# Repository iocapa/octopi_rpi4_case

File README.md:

Shield: [![CC BY-SA 4.0][cc-by-sa-shield]][cc-by-sa]

This work is licensed under a
[Creative Commons Attribution-ShareAlike 4.0 International License][cc-by-sa].

[![CC BY-SA 4.0][cc-by-sa-image]][cc-by-sa]

[cc-by-sa]: http://creativecommons.org/licenses/by-sa/4.0/
[cc-by-sa-image]: https://licensebuttons.net/l/by-sa/4.0/88x31.png
[cc-by-sa-shield]: https://img.shields.io/badge/License-CC%20BY--SA%204.0-lightgrey.svg

## Disclaimer ##
Working with mains voltage can be dangerous. Proceed at your own risk.

## Scope ##
* The scope of this project was to create a case for a raspberry pi4 that runs octopi and provides a way to turn off/on the printer (Prusa MK3S+) via the web interface. 
* The project was designed and built during a weekend, therefore it had to be built with parts/tools I had lying around, and it had to be pretty low effort.
* In retrospective, some design decisions were not the "best", but after running this for a week, I'm pretty satisfied with it :).

## Requirements ##
* Shall use a raspberry pi4.
* Shall be compact enough to fit the available space.
* Shall incorporate a relay controllable through the octoprint interface.
* Shall have a status LED.
* Shall have a safe shutdown / power-on button.
* Shall provide active cooling (fan).
* Shall be installable with minimal effort (no mods to the printer).

## Design (Day 1) ##
* ~~Design the [PCB](./pcb/octopi_rpi4_case.pro)~~.
* ~~Design the case [assembly](./assembly/assembly.pdf)~~.

## Build (Day 2) ##
* Print the [top](./pics/11-top.jpg) part of the case and install the brass inserts.
* Cut and [drill](./pics/1-drill.jpg) the blank PCB using the provided [stencil](./pcb/printable/hole_guide.stl).
* [Mask](./pics/2-mask.jpg) the PCB (with a quality permanent marker) using the [template](./pcb/octopi_rpi4_case_bot_mirrored.pdf).
* [Etch](./pics/3-etch.jpg) the PCB.
* [Tin](./pics/4-tin.jpg) the PCB.
* [Populate](./pics/5-assemble.jpg) the PCB using the [template](./pcb/octopi_rpi4_case_silk.pdf) and the [schematic](./pcb/octopi_rpi4_case.pdf).
* [Coat](./pics/6-coat.jpg) the PCB with a thick plastic layer using the provided [mask](./pcb/printable/coating_mask.stl). <span style="color:red">WARNING SKIP THIS AT YOUR OWN RISK</span>, [ECS Plastic 70](https://www.ecsag.com/product/plastic-2/?lang=en) spray works well.
* Print the [bottom](./pics/10-botom-cap.jpg) part of the case and install the brass inserts, print the switch cap.
* Add connectors to the fans and other cables (power and signal) using the [schematic](./pcb/octopi_rpi4_case.pdf) tables.
* [Prepare](./pics/7-parts.jpg) the parts.
* Assemble the [parts](./pics/8-pre.jpg).
* [Assemble](./pics/9-final.jpg) the case using the [video](./assembly/assembly.mp4) and the [instructions](./assembly/assembly.pdf).
* [Install](https://octoprint.org/download/) on your SD card.
* Copy [boot.txt](./software/boot.txt) and [config.txt](./software/config.txt) to the card. Install the card.
* Unplug the printer cord and connect it to the power input and connect the power output to the printer.
* Instal the [OctoRelay](https://plugins.octoprint.org/plugins/octorelay) plugin and configure the printer relay "GPIO Number" to 15.
* Have fun :)

## Special thanks to ##
* [Hasanain Shuja](https://grabcad.com/hasanain.shuja-1) for the RPi4 step model.
* [John Michael Loeffler](https://grabcad.com/john-772) for the Relay and JST connector step models.
* [KiCAD](https://www.kicad.org/), [Raspberry Pi Foundation](https://www.raspberrypi.org/) and [Fusion 360](https://www.autodesk.com/products/fusion-360/overview) for the awesome tools and resources.

## License ##
A [LICENSE](./LICENSE) file is provided with this repository.

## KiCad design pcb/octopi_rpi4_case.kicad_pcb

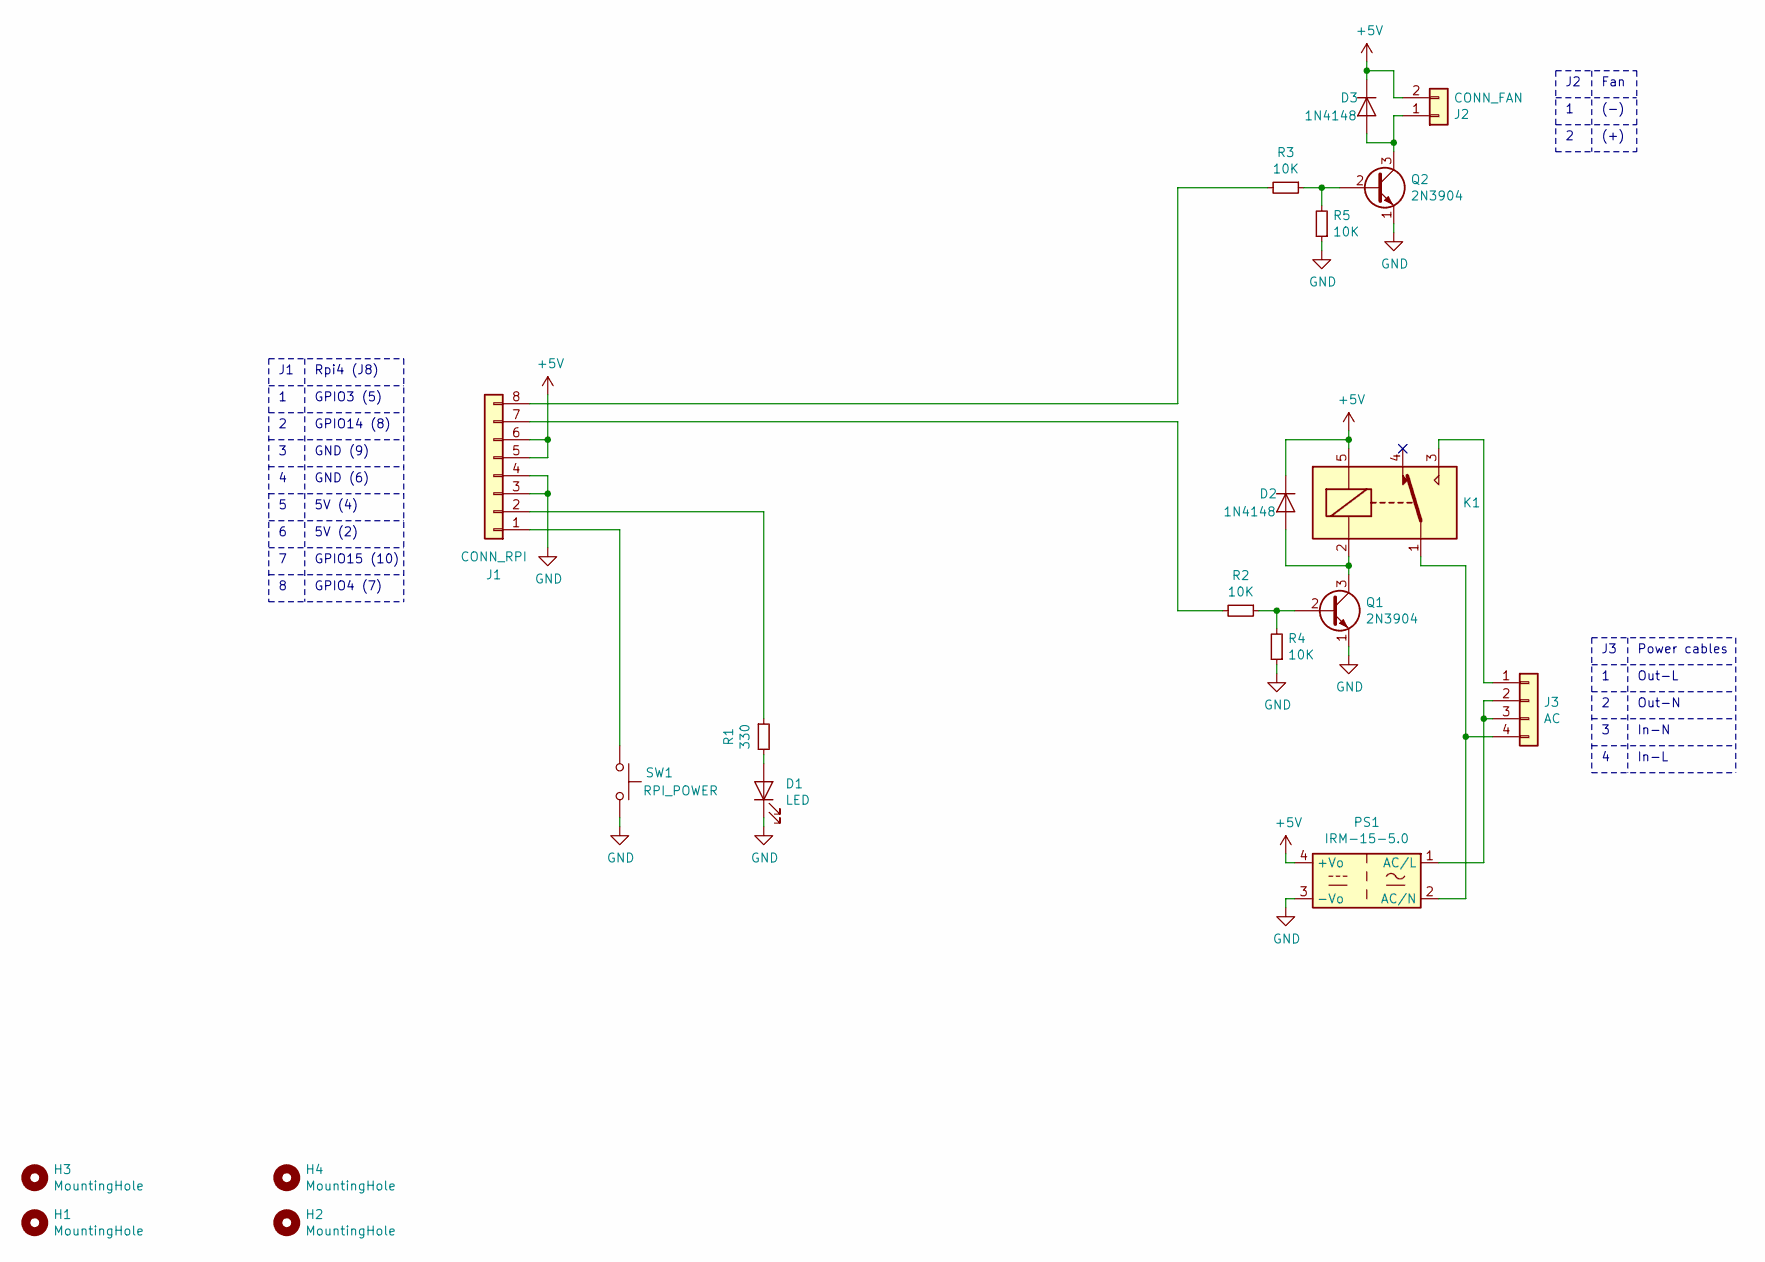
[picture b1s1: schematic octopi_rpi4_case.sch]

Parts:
D1: LED; LED_D5.0mm_Horizontal_O1.27mm_Z3.5mm
D2, D3: 1N4148; D_DO-35_SOD27_P7.62mm_Horizontal
H1, H2, H3, H4: MountingHole; MountingHole_2.7mm
J1: CONN_RPI; Molex_KK-254_AE-6410-08A_1x08_P2.54mm_Vertical
J2: CONN_FAN; Molex_KK-254_AE-6410-02A_1x02_P2.54mm_Vertical
J3: AC; JST_VH_B4P-VH_1x04_P3.96mm_Vertical
K1: SONGLE-SRD-xxVDC-SL-C; Relay_SPDT_SRD-xxVDC-SL-C
PS1: IRM-15-5.0; Converter_ACDC_MeanWell_IRM-15-xx_THT
Q1, Q2: 2N3904; TO-92_Inline_Wide
R1: 330; R_Axial_DIN0207_L6.3mm_D2.5mm_P7.62mm_Horizontal
R2, R3, R4, R5: 10K; R_Axial_DIN0207_L6.3mm_D2.5mm_P7.62mm_Horizontal
SW1: RPI_POWER; SW_Tactile_SPST_Angled_PTS645Vx39-2LFS

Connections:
+5V: D2.1 (K), D3.1 (K), J1.5, J1.6, J2.2, K1.5, PS1.4 (+Vo)
GND: D1.1 (K), J1.3, J1.4, PS1.3 (-Vo), Q1.1 (E), Q2.1 (E), R4.1, R5.1, SW1.1
unnamed: D1.2 (A), R1.2
unnamed: D2.2 (A), K1.2, Q1.3 (C)
unnamed: D3.2 (A), J2.1, Q2.3 (C)
unnamed: J1.1, SW1.2
unnamed: J1.2, R1.1
unnamed: J1.7, R2.2
unnamed: J1.8, R3.2
unnamed: J3.1, K1.3
unnamed: J3.2, J3.3, PS1.1 (AC/L)
unnamed: J3.4, K1.1, PS1.2 (AC/N)
unnamed: Q1.2 (B), R2.1, R4.2
unnamed: Q2.2 (B), R3.1, R5.2

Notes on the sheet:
Power cables
Out-L
Out-N
In-N
In-L
Fan
(-)
(+)
Rpi4 (J8)
5V (2)
5V (4)
GND (6)
GND (9)
GPIO4 (7)
GPIO15 (10)
GPIO3 (5)
GPIO14 (8)

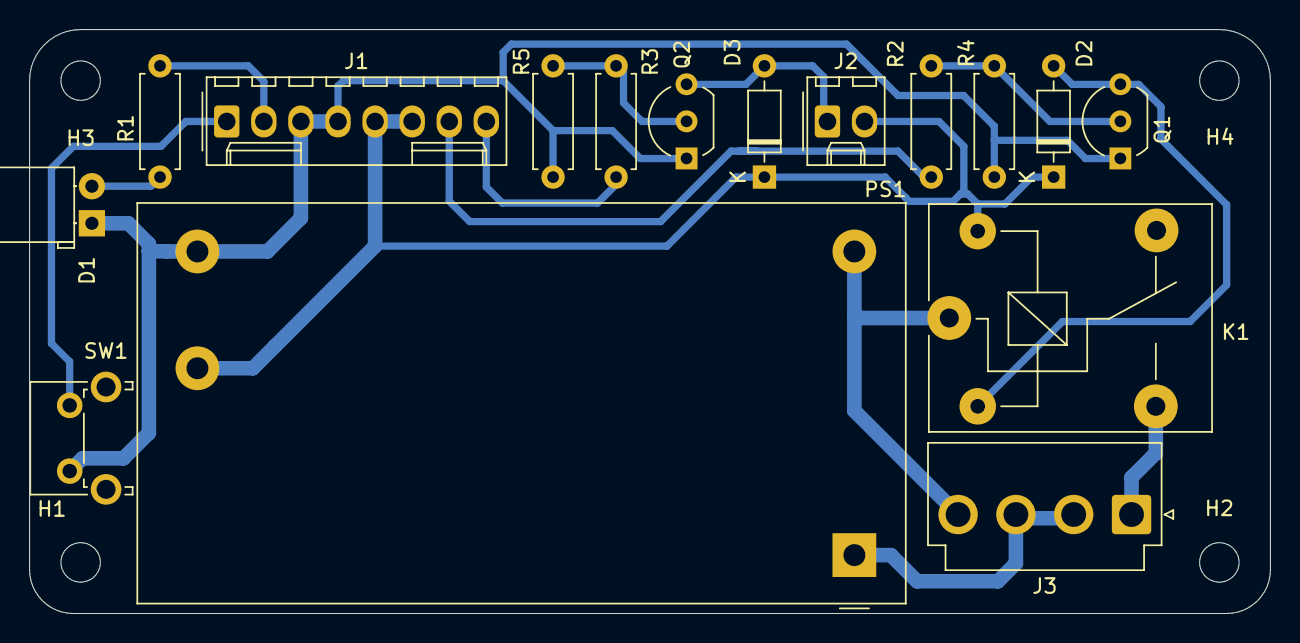
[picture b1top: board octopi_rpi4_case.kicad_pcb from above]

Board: 2 copper layers, 85.0 x 40.0 mm, 20 parts (0 on the bottom side), 14 nets.
